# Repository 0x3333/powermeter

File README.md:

# This project has _not been finished_
# Software is still incomplete
# Looks like I was able to create a sensor in
# ESPurna firmware to handle 3 PZEM004T devices
# So this project is _halted_ until it is eventually needed

[Sensor commit in ESPurna](https://github.com/0x3333/espurna/commit/9d440fd216d5b156dd9e168d6f8793874f21e5dd)

# Power Meter

This project reads multiple PZEM004T readers in the same UART(Support for 6 devices), using Multi-drop TX. It reads all devices constantly and when asked, will send the last reading, synchronously. It uses UART to read the devices and I2C to responde to a master node. I2C Address is `0x33`.

The default implementation is using an Arduino Pro Mini clone(Funduino), the software is using [Simba Framework](https://github.com/eerimoq/simba/).

Folder `pcb` contains the schematics and my PCB version of the reader.

This project support 2 hacks in the PZEM004T:

1. Power direction, allows the reader to know the direction of the power, used in setups with solar panels, etc.
2. Remote reset, allows the reader to reset the counter remotely, without user interaction(Reset all simultaneously, not possible to reset individualy).

These hacks, will be documented here later, the PCB includes 3 mini pcbs that will hold the optocouplers need to isolate the high voltage.

## Info

* The `TX#_EN` pins are used to disable a device `TX` line, so we can set the addresses without user interaction. We force `TX#_EN` `High` on all devices except the one we want to set the address, and then send the set address command. There is a jumper to enable/disable this in case of failure to work.
* `DC_DC` component is a 5V->3.3V converter, I'm using these: [Step-Down Power Supply Buck Module AMS1117](https://www.aliexpress.com/item/10Pcs-5V-To-3-3V-DC-DC-Step-Down-Power-Supply-Buck-Module-AMS1117-800MA/32838774398.html)

## PCB

[Schematic](https://github.com/0x3333/powermeter/raw/master/pcb/schematic.pdf)

[PCB](https://github.com/0x3333/powermeter/raw/master/pcb/pcb.pdf)

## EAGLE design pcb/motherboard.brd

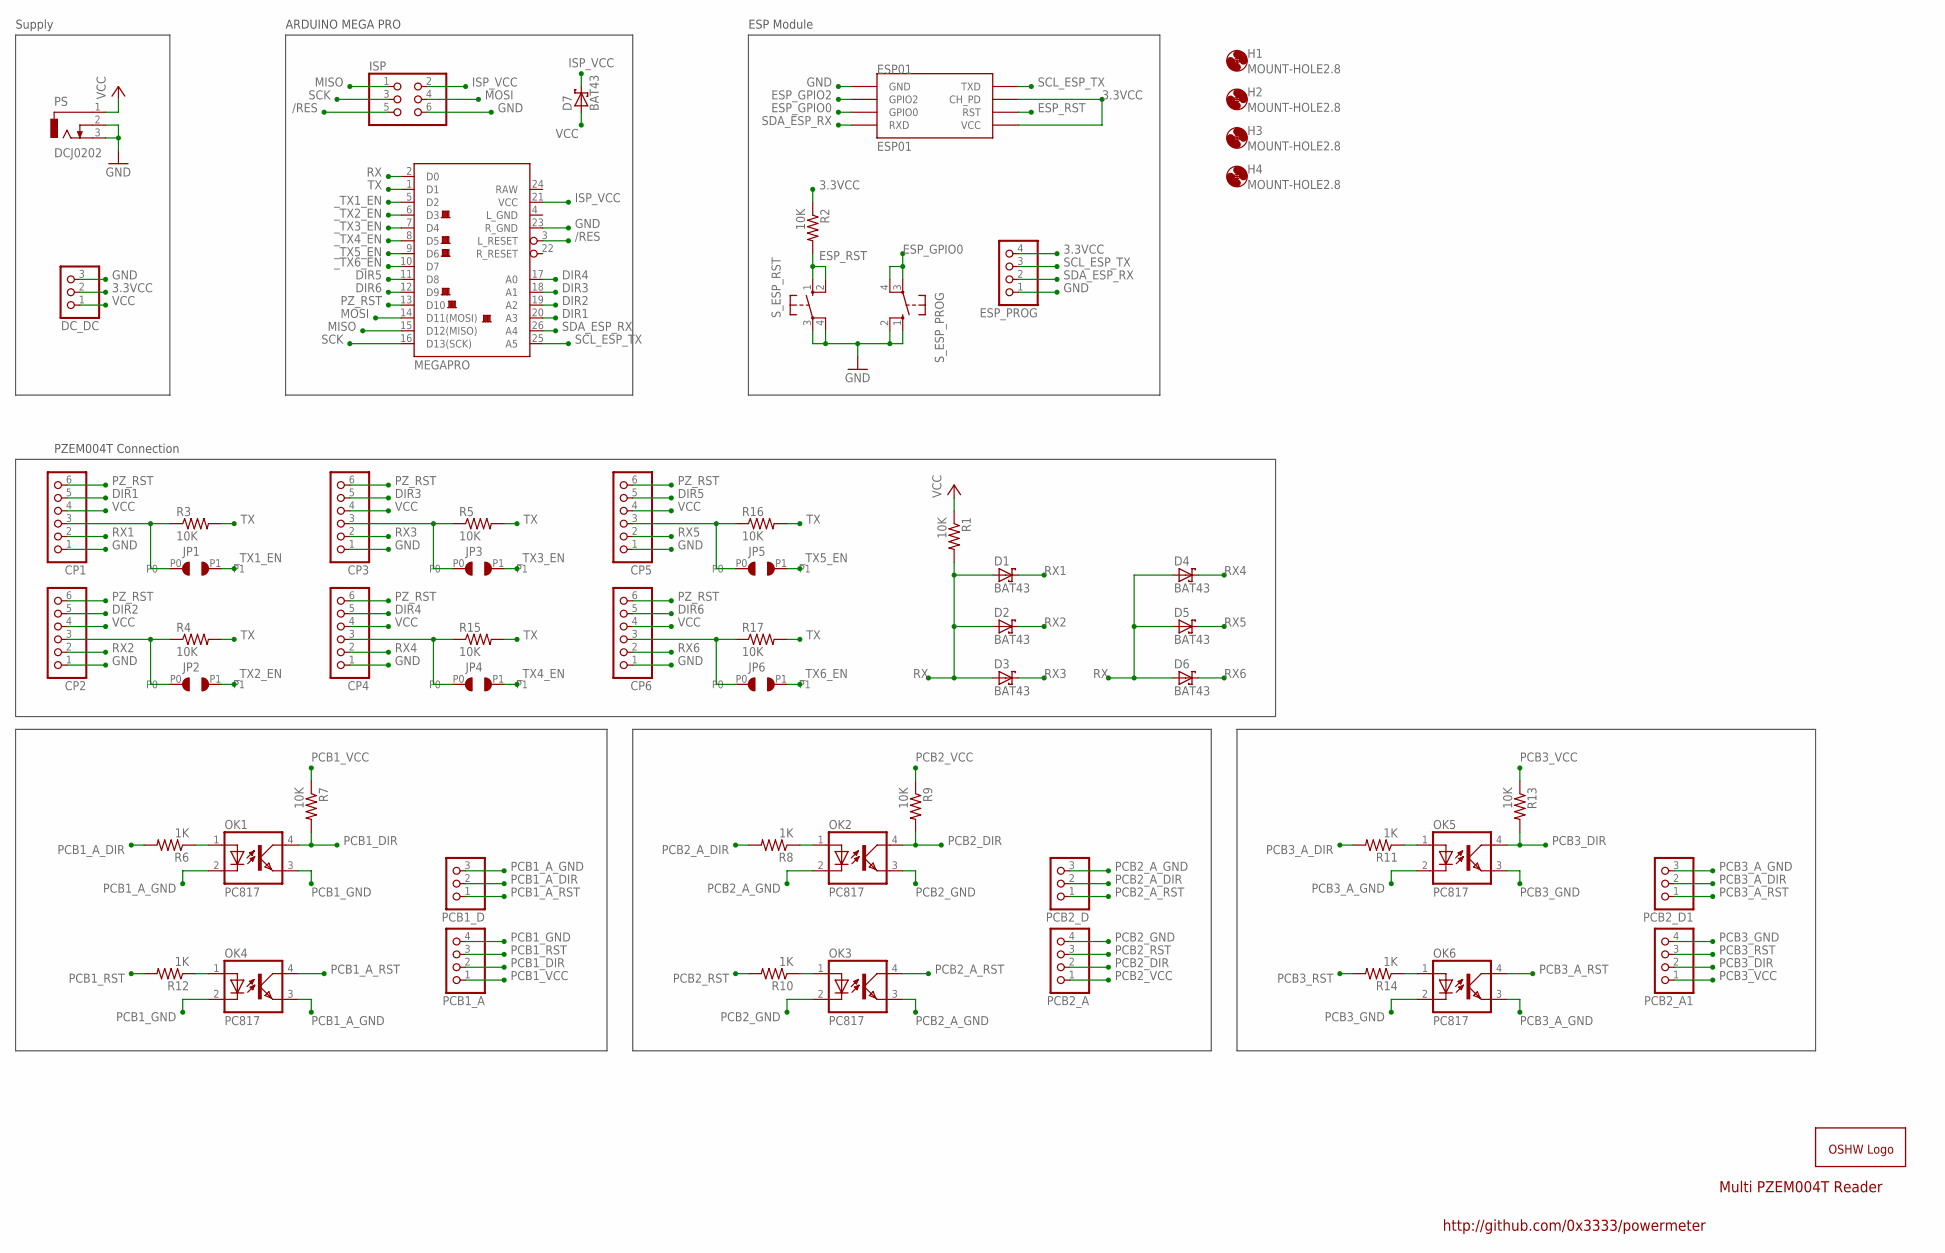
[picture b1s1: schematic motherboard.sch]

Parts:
CP1, CP2, CP3, CP4, CP5, CP6: PINHD-1X6; 1X06
D1, D2, D3, D4, D5, D6, D7: BAT43; SOD323_ST
DC_DC: PINHD-1X3; 1X03
ESP01: ESP01
ESP_PROG: PINHD-1X4; 1X04
GOLD_ORB_SM1: OSHWLOGOLOGO8MM; OSHW_8MM
H1, H2, H3, H4: MOUNT-HOLE2.8; 2,8
ISP: PINHD-2X3; 2X03
JP1, JP2, JP3, JP4, JP5, JP6: SMD_JUMPER
MEGAPRO: ARDUINO_PRO_MINI
OK1, OK2, OK3, OK4, OK5, OK6: PC817; DIL04
PCB1_A, PCB2_A, PCB2_A1: PINHD-1X4; 1X04
PCB1_D, PCB2_D, PCB2_D1: PINHD-1X3; 1X03
PS: DCJ0202
R1, R3, R4, R5, R15, R16, R17: 10K; R1206W
R2, R7, R9, R13: 10K; R0805
R6, R8, R10, R11, R12, R14: 1K; R0805
S_ESP_PROG: 10-XX; B3F-10XX
S_ESP_RST: 10-XX; B3F-10XX

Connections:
3.3VCC: DC_DC.2, ESP01.CH_PD, ESP01.VCC, ESP_PROG.4, R2.1
/RES: ISP.5, MEGAPRO.3 (L_RESET)
DIR1: CP1.5, MEGAPRO.20 (A3)
DIR2: CP2.5, MEGAPRO.19 (A2)
DIR3: CP3.5, MEGAPRO.18 (A1)
DIR4: CP4.5, MEGAPRO.17 (A0)
DIR5: CP5.5, MEGAPRO.11 (D8)
DIR6: CP6.5, MEGAPRO.12 (D9)
ESP_GPIO0: ESP01.GPIO0, S_ESP_PROG.3, S_ESP_PROG.4 (P1)
ESP_GPIO2: ESP01.GPIO2
ESP_RST: ESP01.RST, R2.2, S_ESP_RST.1 (S), S_ESP_RST.2 (S1)
GND: CP1.1, CP2.1, CP3.1, CP4.1, CP5.1, CP6.1, DC_DC.3, ESP01.GND, ESP_PROG.1, ISP.6, MEGAPRO.23 (R_GND), PS.2, PS.3, S_ESP_PROG.1 (S), S_ESP_PROG.2 (S1), S_ESP_RST.3, S_ESP_RST.4 (P1)
ISP_VCC: D7.C, ISP.2, MEGAPRO.21 (VCC)
MISO: ISP.1, MEGAPRO.15 (D12(MISO))
MOSI: ISP.4, MEGAPRO.14 (D11(MOSI))
unnamed: CP1.3, JP1.P0, R3.1
unnamed: CP2.3, JP2.P0, R4.1
unnamed: OK1.1 (A), R6.1
unnamed: CP3.3, JP3.P0, R5.1
unnamed: OK2.1 (A), R8.1
unnamed: OK3.1 (A), R10.1
unnamed: OK5.1 (A), R11.1
unnamed: OK6.1 (A), R14.1
unnamed: CP4.3, JP4.P0, R15.1
unnamed: CP5.3, JP5.P0, R16.1
unnamed: CP6.3, JP6.P0, R17.1
unnamed: OK4.1 (A), R12.1
PCB1_A_DIR: PCB1_D.2, R6.2
PCB1_A_GND: OK1.2 (C), OK4.3 (EMIT), PCB1_D.3
PCB1_A_RST: OK4.4 (COL), PCB1_D.1
PCB1_DIR: OK1.4 (COL), PCB1_A.2, R7.2
PCB1_GND: OK1.3 (EMIT), OK4.2 (C), PCB1_A.4
PCB1_RST: PCB1_A.3, R12.2
PCB1_VCC: PCB1_A.1, R7.1
PCB2_A_DIR: PCB2_D.2, R8.2
PCB2_A_GND: OK2.2 (C), OK3.3 (EMIT), PCB2_D.3
PCB2_A_RST: OK3.4 (COL), PCB2_D.1
PCB2_DIR: OK2.4 (COL), PCB2_A.2, R9.2
PCB2_GND: OK2.3 (EMIT), OK3.2 (C), PCB2_A.4
PCB2_RST: PCB2_A.3, R10.2
PCB2_VCC: PCB2_A.1, R9.1
PCB3_A_DIR: PCB2_D1.2, R11.2
PCB3_A_GND: OK5.2 (C), OK6.3 (EMIT), PCB2_D1.3
PCB3_A_RST: OK6.4 (COL), PCB2_D1.1
PCB3_DIR: OK5.4 (COL), PCB2_A1.2, R13.2
PCB3_GND: OK5.3 (EMIT), OK6.2 (C), PCB2_A1.4
PCB3_RST: PCB2_A1.3, R14.2
PCB3_VCC: PCB2_A1.1, R13.1
PZ_RST: CP1.6, CP2.6, CP3.6, CP4.6, CP5.6, CP6.6, MEGAPRO.13 (D10)
RX: D1.A, D2.A, D3.A, D4.A, D5.A, D6.A, MEGAPRO.2 (D0), R1.2
RX1: CP1.2, D1.C
RX2: CP2.2, D2.C
RX3: CP3.2, D3.C
RX4: CP4.2, D4.C
RX5: CP5.2, D5.C
RX6: CP6.2, D6.C
SCK: ISP.3, MEGAPRO.16 (D13(SCK))
SCL_ESP_TX: ESP01.TX (TXD), ESP_PROG.3, MEGAPRO.25 (A5)
SDA_ESP_RX: ESP01.RX (RXD), ESP_PROG.2, MEGAPRO.26 (A4)
TX: MEGAPRO.1 (D1), R3.2, R4.2, R5.2, R15.2, R16.2, R17.2
VCC: CP1.4, CP2.4, CP3.4, CP4.4, CP5.4, CP6.4, D7.A, DC_DC.1, PS.1, R1.1
_TX1_EN: JP1.P1, MEGAPRO.5 (D2)
_TX2_EN: JP2.P1, MEGAPRO.6 (D3)
_TX3_EN: JP3.P1, MEGAPRO.7 (D4)
_TX4_EN: JP4.P1, MEGAPRO.8 (D5)
_TX5_EN: JP5.P1, MEGAPRO.9 (D6)
_TX6_EN: JP6.P1, MEGAPRO.10 (D7)

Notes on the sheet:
ESP Module
Supply
PZEM004T Connection
ARDUINO MEGA PRO
Multi PZEM004T Reader
http://github.com/0x3333/powermeter

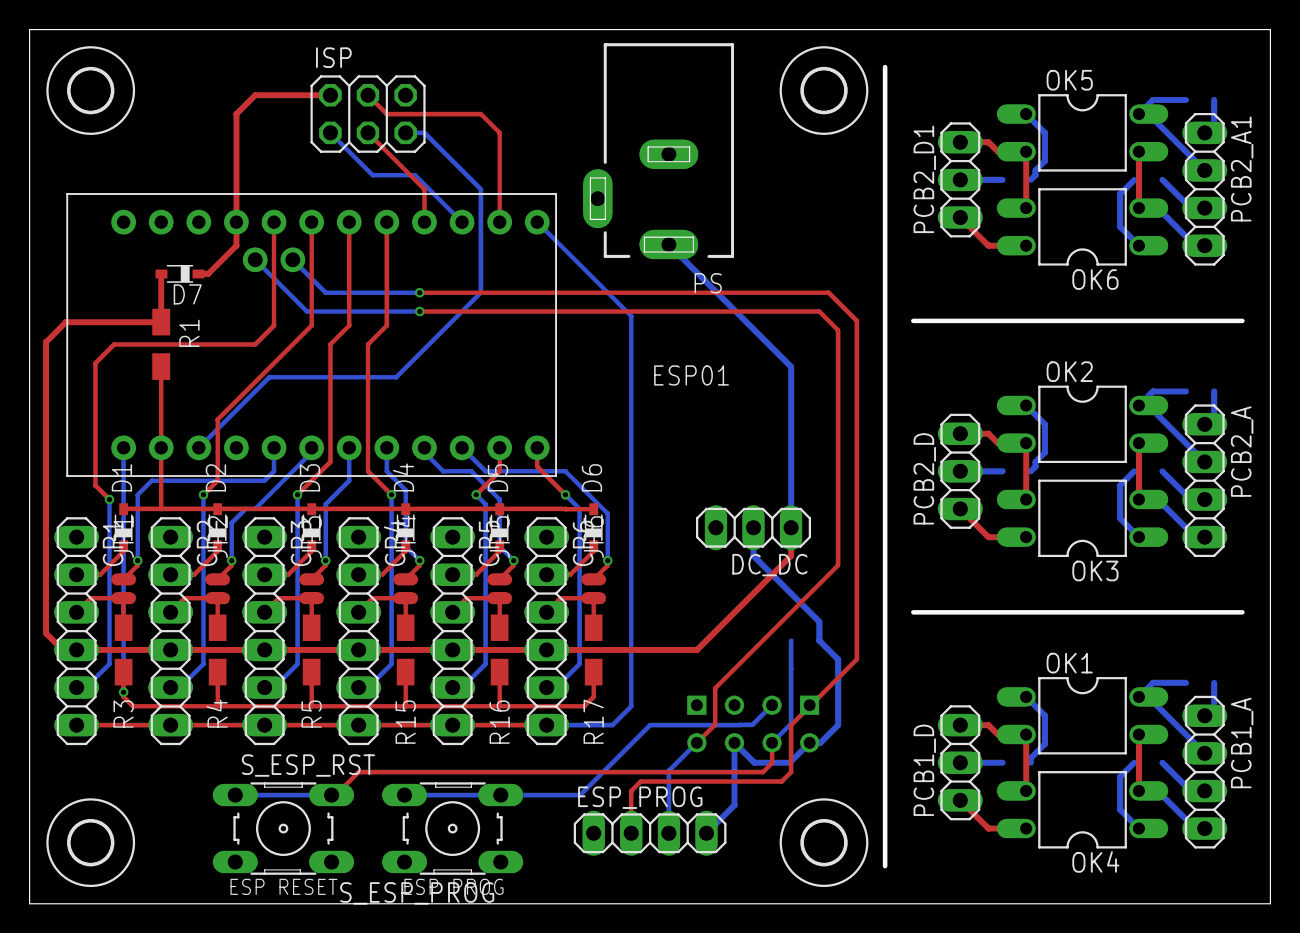
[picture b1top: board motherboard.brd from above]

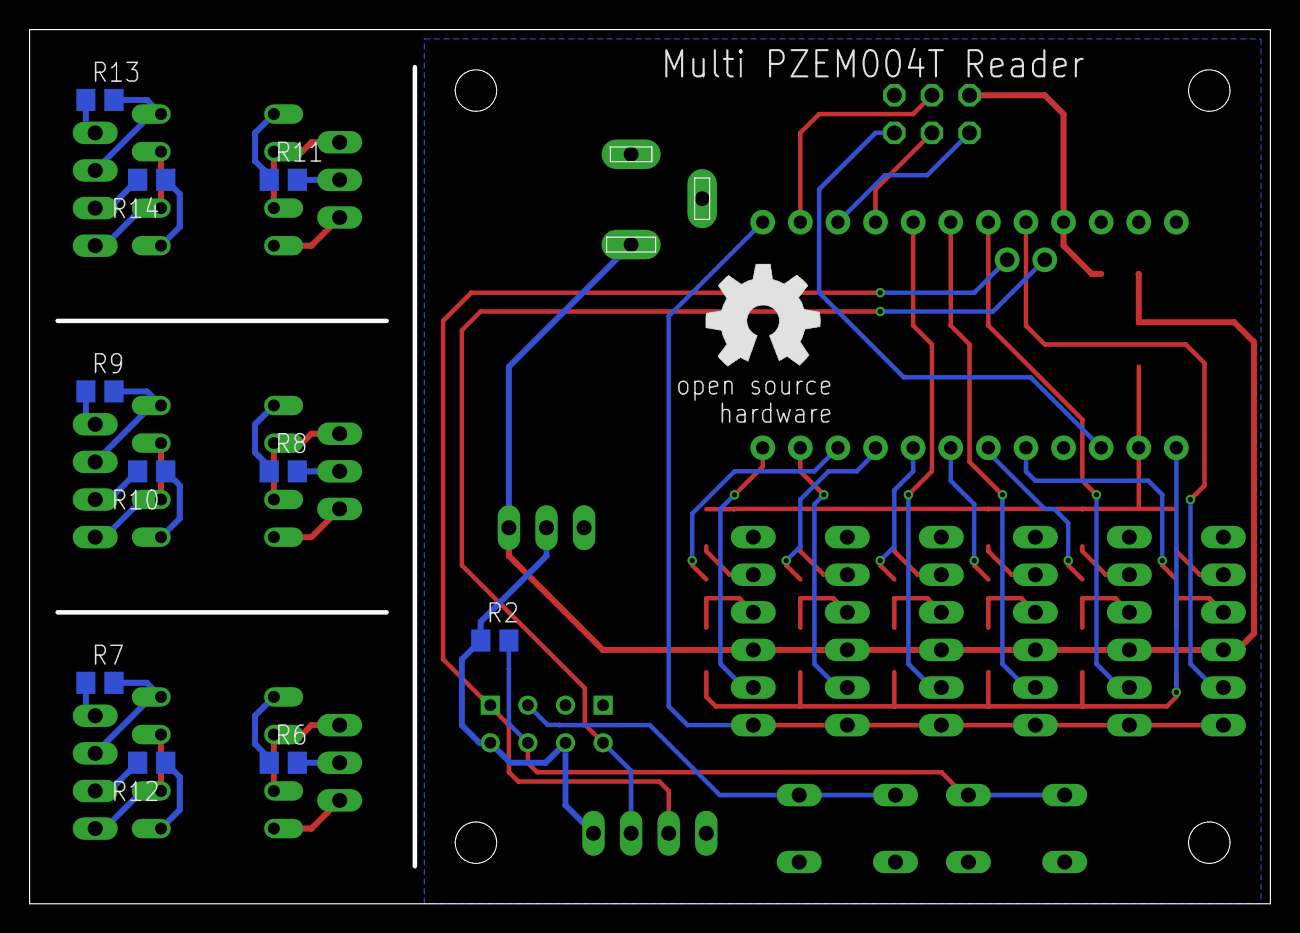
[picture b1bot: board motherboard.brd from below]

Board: 2 copper layers, 83.5 x 58.7 mm, 61 parts (11 on the bottom side), 66 nets.

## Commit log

2018-07-23 Initial code.
2018-07-23 Removed old header.
2018-08-30 Fixed incorrect binary.
2018-10-14 Initial implementation. First PCB revision.
2018-10-14 Fixed README.md
2018-10-15 Modified to support 6 devices.
2018-10-15 Added Schematic image and links.
2018-10-15 Added PCB files.
2018-10-15 Small fix.
2018-10-15 Added info.
2018-10-15 Updated PCB/Schematic.
2018-10-16 Working on pzem004t reader code.
